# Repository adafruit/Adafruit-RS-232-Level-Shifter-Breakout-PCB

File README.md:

## Adafruit RS-232 Full Pinout Level-Shifter Breakout PCB

<a href="http://www.adafruit.com/products/5988"><br/>
Click here to purchase one from the Adafruit shop</a>

PCB files for the Adafruit RS-232 Full Pinout Level-Shifter Breakout. 

Format is EagleCAD schematic and board layout
* https://www.adafruit.com/product/5988

### Description

If you want to interface with telco, retro, or industrial equipment, you'll probably run into RS-232 interfaces. The Adafruit RS232 Full-Pinout Breakout with 8 Channels of UART to RS-232 Level Shifters is your friend in such cases. It gives you 5 input and 3 output channels of level shifting and takes care of the high/negative voltage generation all in a low-cost breakout board. We use the trusty MAX3243 from TI, a classic chip part of the MAX232 lineage, so you know it will work great for all your RS-232 needs, up to 250Kbps.

RS-232 is what we had before USB: a 9- or 25-pin D-Sub connector that allowed data plus flow control lines. Many folks may remember these interfaces were used for mice, modems, barcode scanners, teletypes, and more. We still find devices sold with RS-232 ports, although many folks use a USB to RS-232 adapter these days.

If you want to use a microcontroller or microcomputer to chat with an RS-232, then thankfully, all you need is a serial port / UART (something just about any microcontroller has) and a level shifter. The level shifter is required because while most UARTs are 0-3.3V or 0-5V logic level, RS-232 requires +-6 to +-10V, yep the signal voltage goes negative! That means a specialized shifter is required to generate extra high and low voltages and safely convert the logic levels.

Sure you could buy a raw MAX232 chip and wire up the necessary capacitors, but this board does it all for you and even comes with a DE-9 connector for plugging in directly into your 'client' device. It can run on 3.3V power and logic, which many older chips can't do. It also can do all 8 data pins, so you can use all of the flow control signals like RTS, CTS, DTR, DSR, DCD and RI.

We also include two separate lines from the MAX3243: 'Valid' and 'Off'. The Valid line output will have logic level high when the chip detects signal voltages from the device its plugged into. So you can use it as a 'connection made' signal. There's also the Off pin, which when set to logic high by the microcontroller will tri-state all the pins for power reduction.

This breakout comes fully assembled with a UART side for low-voltage power/logic level, and a DE-9F RS-232 side for high-voltage signals. We also include some header so you can solder to a breadboard in a few minutes.

### License

Adafruit invests time and resources providing this open source design, please support Adafruit and open-source hardware by purchasing products from [Adafruit](https://www.adafruit.com)!

Designed by Limor Fried/Ladyada for Adafruit Industries.

Creative Commons Attribution/Share-Alike, all text above must be included in any redistribution. 
See license.txt for additional details.

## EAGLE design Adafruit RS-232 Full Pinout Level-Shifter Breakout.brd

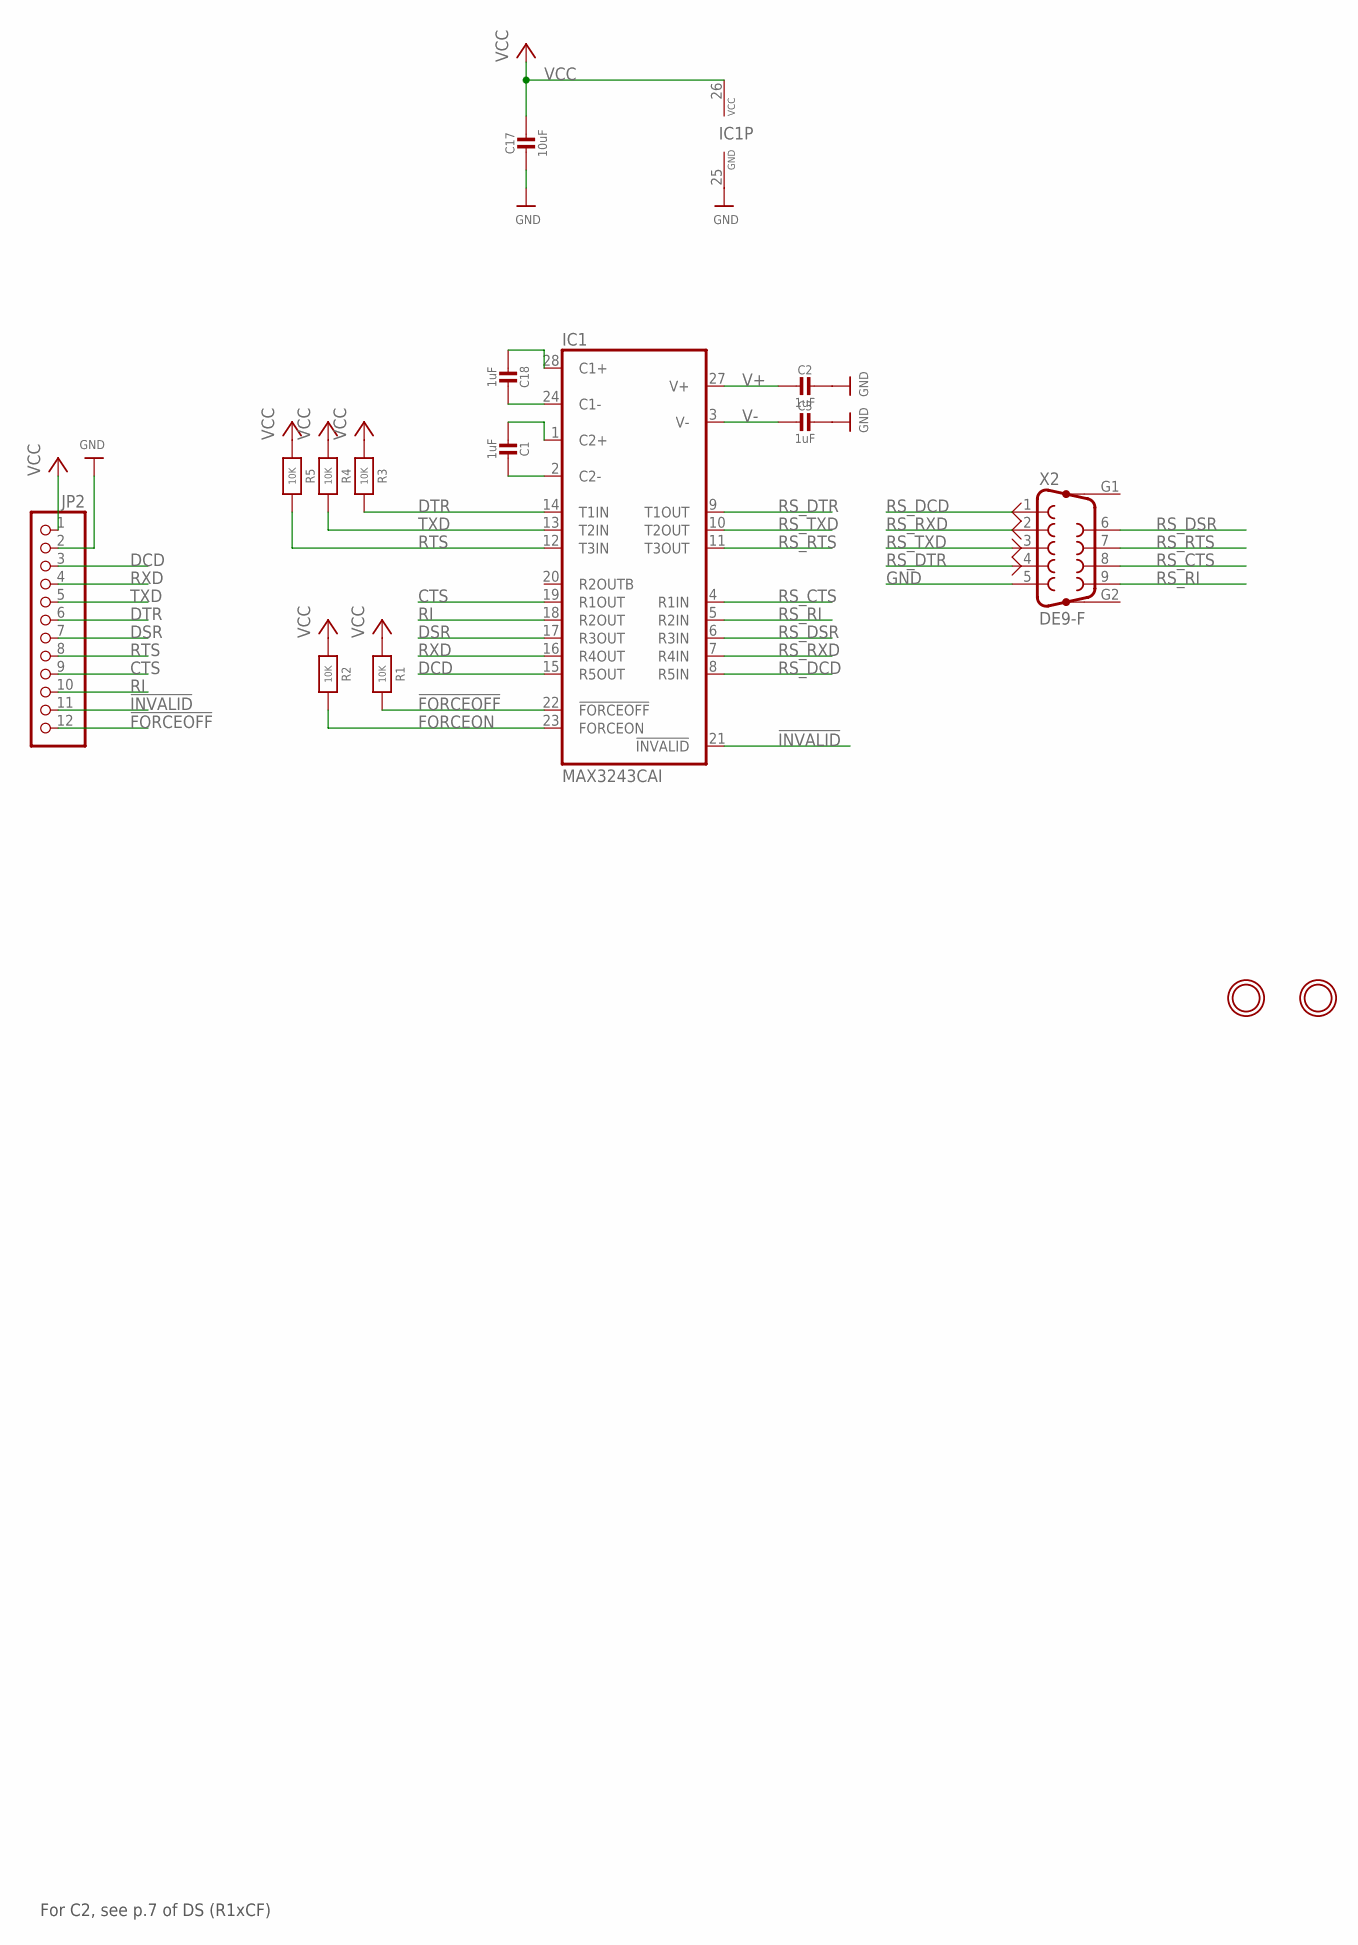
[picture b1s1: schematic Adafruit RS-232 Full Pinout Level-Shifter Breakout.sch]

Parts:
C1, C2, C3, C18: 1uF; 0603-NO
C17: 10uF; 0805-NO
IC1: MAX3243CAI; SSOP28
JP2: HEADER-1X1276MIL; 1X12_ROUND_76MIL
R1, R2, R3, R4, R5: 10K; 0603-NO
U$2, U$3: MOUNTINGHOLE3.0THIN; MOUNTINGHOLE_3.0_PLATEDTHIN
X2: DE9-F; F09HP

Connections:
!FORCEOFF: IC1.22 (!FORCEOFF), JP2.12, R1.2
!INVALID: IC1.21 (!INVALID), JP2.11
CTS: IC1.19 (R1OUT), JP2.9
DCD: IC1.15 (R5OUT), JP2.3
DSR: IC1.17 (R3OUT), JP2.7
DTR: IC1.14 (T1IN), JP2.6, R3.2
FORCEON: IC1.23 (FORCEON), R2.2
GND: C2.1, C3.1, C17.2, IC1.25 (GND), JP2.2, X2.5
unnamed: C18.2, IC1.28 (C1+)
unnamed: C18.1, IC1.24 (C1-)
unnamed: C1.1, IC1.2 (C2-)
unnamed: C1.2, IC1.1 (C2+)
RI: IC1.18 (R2OUT), JP2.10
RS_CTS: IC1.4 (R1IN), X2.8
RS_DCD: IC1.8 (R5IN), X2.1
RS_DSR: IC1.6 (R3IN), X2.6
RS_DTR: IC1.9 (T1OUT), X2.4
RS_RI: IC1.5 (R2IN), X2.9
RS_RTS: IC1.11 (T3OUT), X2.7
RS_RXD: IC1.7 (R4IN), X2.2
RS_TXD: IC1.10 (T2OUT), X2.3
RTS: IC1.12 (T3IN), JP2.8, R5.2
RXD: IC1.16 (R4OUT), JP2.4
TXD: IC1.13 (T2IN), JP2.5, R4.2
V+: C2.2, IC1.27 (V+)
V-: C3.2, IC1.3 (V-)
VCC: C17.1, IC1.26 (VCC), JP2.1, R1.1, R2.1, R3.1, R4.1, R5.1

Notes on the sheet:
For C2, see p.7 of DS (R1xCF)

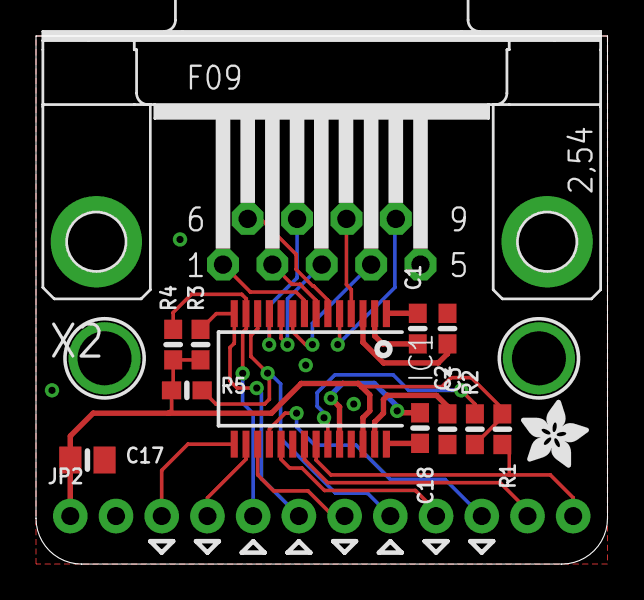
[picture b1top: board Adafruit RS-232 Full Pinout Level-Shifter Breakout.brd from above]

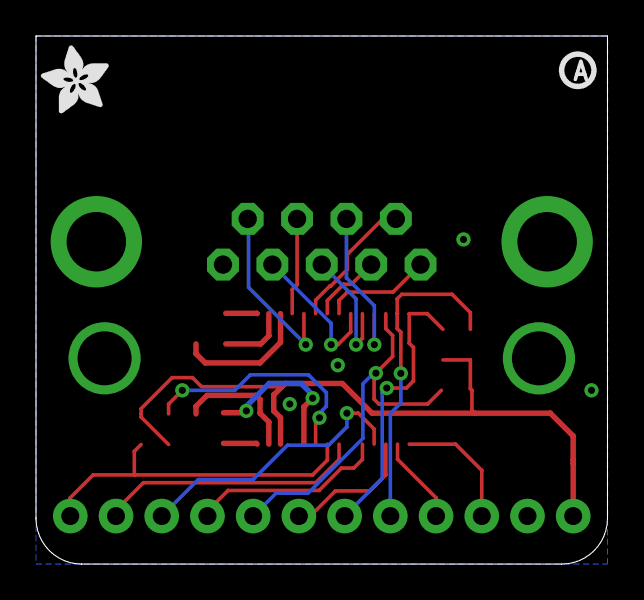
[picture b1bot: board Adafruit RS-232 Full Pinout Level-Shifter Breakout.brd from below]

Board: 2 copper layers, 31.8 x 29.3 mm, 34 parts (5 on the bottom side), 27 nets.

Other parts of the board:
PLABEL0: PLABEL0
PLABEL1: PLABEL1
PLABEL2: PLABEL2
PLABEL3: PLABEL3
PLABEL4: PLABEL4
PLABEL5: PLABEL5
PLABEL6: PLABEL6
PLABEL7: PLABEL7
PLABEL8: PLABEL8
PLABEL9: PLABEL9
PLABEL10: PLABEL10
PLABEL11: PLABEL11
PLABEL12: PLABEL12
PLABEL13: PLABEL13
PLABEL14: PLABEL14
PLABEL15: PLABEL15
U$5: PCBFEAT-REV-040
U$8, U$9: ADAFRUIT_3.5MM

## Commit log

2024-08-12 cookiecutter
2024-08-12 Create Adafruit RS-232 Full Pinout Level-Shifter Breakout.s##
2024-08-12 Revert "Create Adafruit RS-232 Full Pinout Level-Shifter Breakout.s##"
    This reverts commit 1730bd0751fbcb88c8bee007e2b72b5eb968e2de.

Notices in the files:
parts and their libraries:
microbuilder: This work is placed in the public domain, and may be freely used for commercial and non-commercial work with the following conditions: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
